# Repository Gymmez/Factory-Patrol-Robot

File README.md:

# 🤖 Za3tar Robot Project

This project shows a robot camera stream and sensor pages in a web browser.

You do not need to install Python. Docker will run everything for you.

## 📦 What You Need

Install these programs:

1. [Docker Desktop](https://www.docker.com/products/docker-desktop/)
2. [Git](https://git-scm.com/downloads)
3. A working camera or phone camera stream

After installing Docker Desktop, open it and wait until it says Docker is
running.

## 1️⃣ Download the Project

Open a terminal:

- **Windows:** open PowerShell
- **Mac:** open Terminal
- **Linux:** open Terminal

Run:

```bash
git clone --recurse-submodules <repository-url>
cd Factory-Patrol-Robot
```

Ask the person who gave you the project for the repository URL.

The `--recurse-submodules` option downloads the `analog_gauge_reader` model
project. If you already cloned the project without submodules, run this from
inside the project folder:

```bash
git submodule update --init --recursive
```

## 2️⃣ Enter the Camera Stream Address

This project needs the address of the camera's MJPEG stream.

The address commonly looks like:

```text
http://192.168.1.50:8080/video
```

Do not use `localhost` or `127.0.0.1`. These addresses refer to the
Docker container, not your camera.

### 📝 Create the settings file

Copy `.env.example` to `.env`:

**Windows PowerShell:**

```powershell
Copy-Item .env.example .env
```

**Mac and Linux:**

```bash
cp .env.example .env
```

Open `.env` in a text editor and replace the address:

```dotenv
MJPEG_STREAM_URL=http://192.168.1.50:8080/video
```

Save the file.

## 3️⃣ Start the Project

In the project folder, run:

```bash
docker compose up -d --build
```

The first start may take a while. Docker must download the database and build
the application. It can take 10 minutes or longer depending on your internet
connection.

Do not close Docker Desktop while building or starting the project.

## 4️⃣ Open the Website

Open a browser and visit:

```text
http://localhost:8000
```

Useful pages:

- Home: http://localhost:8000
- Sensors: http://localhost:8000/sensors
- Camera stream: http://localhost:8000/stream
- Robot controls: http://localhost:8000/control
- Health check: http://localhost:8000/health
- API documentation: http://localhost:8000/docs

## 5️⃣ Change the Camera Address

To use another camera address:

1. Open `.env`.
2. Change `MJPEG_STREAM_URL`.
3. Save the file.
4. Run:

```bash
docker compose up -d --force-recreate api
```

Refresh the website.

## ✅ Check Whether It Is Working

Run:

```bash
docker compose ps
```

You should see the `api` and `db` containers running.

For the health check:

```bash
curl http://localhost:8000/health
```

A successful response is:

```json
{"status":"ok"}
```

If the camera is not visible, confirm that:

- The camera address is correct.
- The address works from a normal browser or phone.
- The address is reachable from the computer running Docker.
- The address ends with the correct video path.

## 🛑 Stop the Project

Keep the saved data and stop the containers:

```bash
docker compose down
```

Start it again later:

```bash
docker compose up -d
```

## 🔄 Reset Everything

This permanently deletes all saved database data.

```bash
docker compose down -v
docker compose up -d --build
```

Only use this command when a complete reset is wanted.

## 🧰 If Something Goes Wrong

### ⚠️ The project does not start

Check that Docker Desktop is running, then run:

```bash
docker compose up --build
```

Reading the messages in the terminal can show whether Docker is downloading
or building something.

### 📹 The camera does not appear

Open the camera address directly in a browser.

Example:

```text
http://192.168.1.50:8080/video
```

If that address does not open in the browser, the application cannot receive
the stream.

### 🔍 Show recent errors

```bash
docker compose logs api
docker compose logs db
```

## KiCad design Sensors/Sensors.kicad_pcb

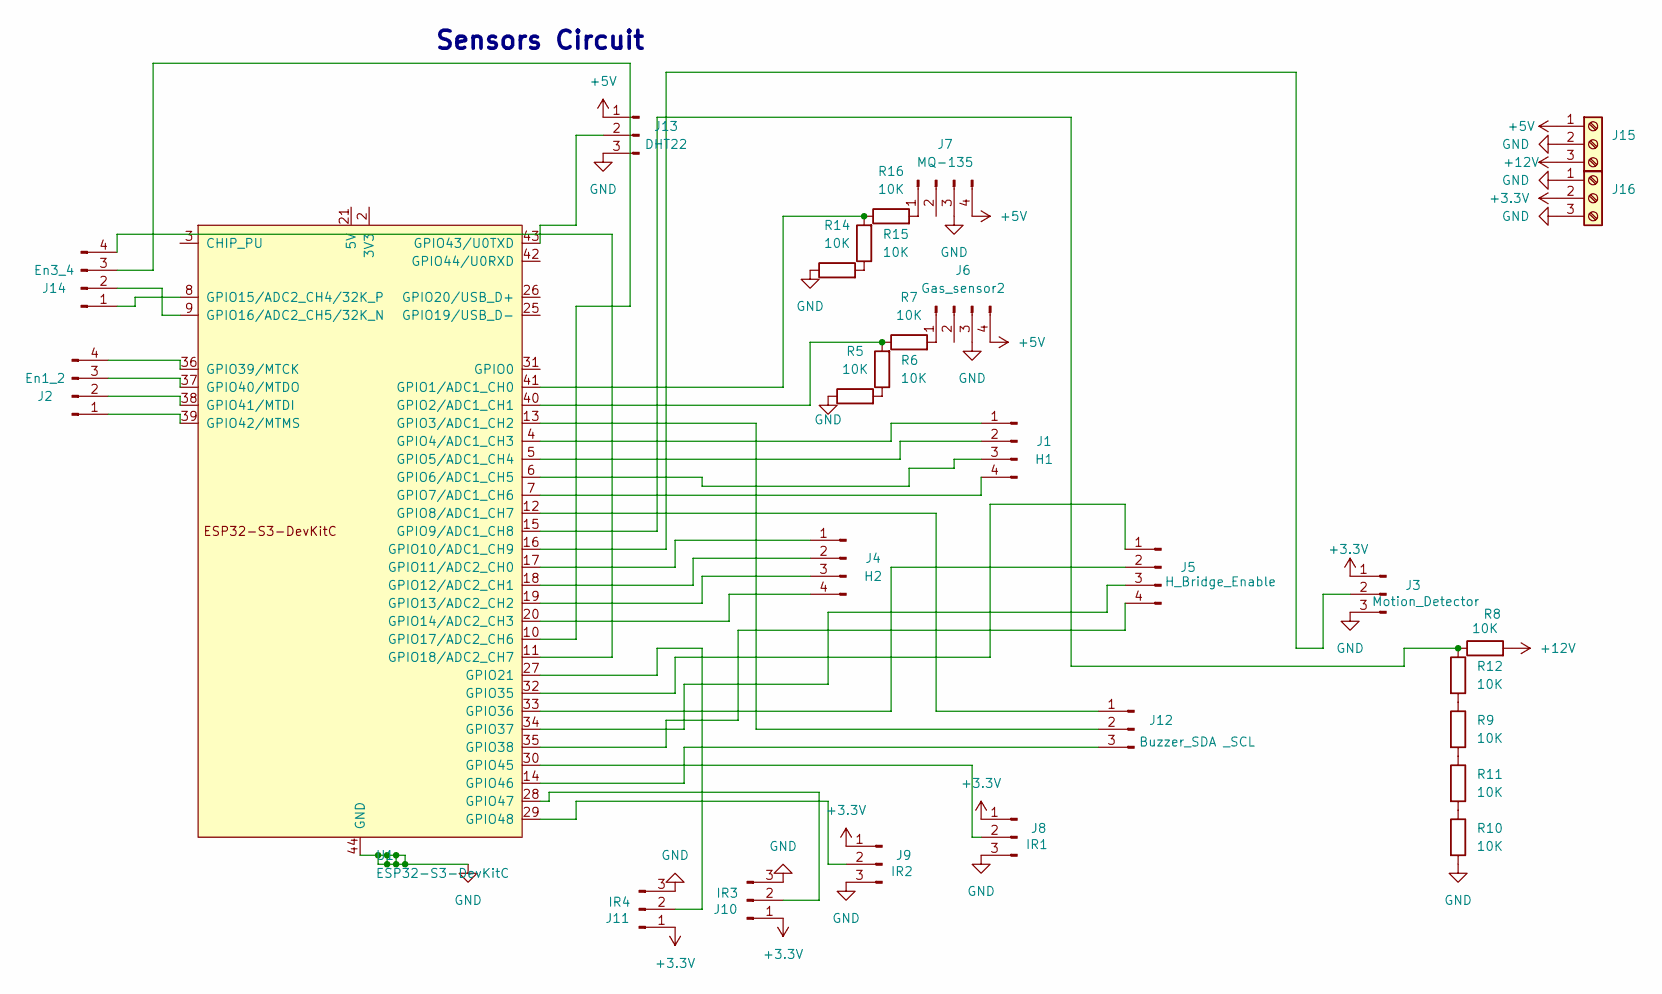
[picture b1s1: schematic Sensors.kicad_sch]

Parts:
J1: H1; PinSocket_1x04_P2.54mm_Vertical
J2: En1_2; PinSocket_1x04_P2.54mm_Vertical
J3: Motion_Detector; PinSocket_1x03_P2.54mm_Vertical
J4: H2; PinSocket_1x04_P2.54mm_Vertical
J5: H_Bridge_Enable; PinSocket_1x04_P2.54mm_Vertical
J6: Gas_sensor2; PinSocket_1x04_P2.54mm_Vertical
J7: MQ-135; PinSocket_1x04_P2.54mm_Vertical
J8: IR1; PinSocket_1x03_P2.54mm_Vertical
J9: IR2; PinSocket_1x03_P2.54mm_Vertical
J10: IR3; PinSocket_1x03_P2.54mm_Vertical
J11: IR4; PinSocket_1x03_P2.54mm_Vertical
J12: Buzzer_SDA _SCL; PinSocket_1x03_P2.54mm_Vertical
J13: DHT22; PinSocket_1x03_P2.54mm_Vertical
J14: En3_4; PinSocket_1x04_P2.54mm_Vertical
J15, J16: Screw_Terminal_01x03; TerminalBlock_Phoenix_MKDS-3-3-5.08_1x03_P5.08mm_Horizontal
R5, R6, R7, R8, R9, R10, R11, R12, R14, R15, R16: 10K; R_Axial_DIN0207_L6.3mm_D2.5mm_P7.62mm_Horizontal
U1: ESP32-S3-DevKitC

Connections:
+3.3V: J3.1, J8.1, J9.1, J10.1, J11.1, J16.2
+5V: J6.4, J7.4, J13.1, J15.1
+12V: J15.3, R8.2
GND: J3.3, J6.3, J7.3, J8.3, J9.3, J10.3, J11.3, J13.3, J15.2, J16.1, J16.3, R5.1, R10.2, R14.1, U1.22 (GND), U1.23 (GND), U1.24 (GND), U1.44 (GND)
unnamed: J1.1, U1.4 (GPIO4/ADC1_CH3)
unnamed: J1.2, U1.5 (GPIO5/ADC1_CH4)
unnamed: J1.3, U1.6 (GPIO6/ADC1_CH5)
unnamed: J1.4, U1.7 (GPIO7/ADC1_CH6)
unnamed: J2.1, U1.39 (GPIO42/MTMS)
unnamed: J2.2, U1.38 (GPIO41/MTDI)
unnamed: J2.3, U1.37 (GPIO40/MTDO)
unnamed: J2.4, U1.36 (GPIO39/MTCK)
unnamed: J3.2, U1.16 (GPIO10/ADC1_CH9)
unnamed: J4.1, U1.17 (GPIO11/ADC2_CH0)
unnamed: J4.2, U1.18 (GPIO12/ADC2_CH1)
unnamed: J4.3, U1.19 (GPIO13/ADC2_CH2)
unnamed: J4.4, U1.20 (GPIO14/ADC2_CH3)
unnamed: J5.1, U1.32 (GPIO35)
unnamed: J5.2, U1.33 (GPIO36)
unnamed: J5.3, U1.34 (GPIO37)
unnamed: J5.4, U1.35 (GPIO38)
unnamed: J6.1, R7.2
unnamed: J7.1, R16.2
unnamed: J8.2, U1.30 (GPIO45)
unnamed: J9.2, U1.29 (GPIO48)
unnamed: J10.2, U1.28 (GPIO47)
unnamed: J11.2, U1.27 (GPIO21)
unnamed: J12.1, U1.12 (GPIO8/ADC1_CH7)
unnamed: J12.2, U1.13 (GPIO3/ADC1_CH2)
unnamed: J12.3, U1.14 (GPIO46)
unnamed: J13.2, U1.43 (GPIO43/U0TXD)
unnamed: J14.1, U1.8 (GPIO15/ADC2_CH4/32K_P)
unnamed: J14.2, U1.9 (GPIO16/ADC2_CH5/32K_N)
unnamed: J14.3, U1.10 (GPIO17/ADC2_CH6)
unnamed: J14.4, U1.11 (GPIO18/ADC2_CH7)
unnamed: R5.2, R6.1
unnamed: R10.1, R11.2
unnamed: R9.2, R11.1
unnamed: R9.1, R12.2
unnamed: R14.2, R15.1
unnamed: U1.1 (3V3), U1.2 (3V3)
unnamed: R15.2, R16.1, U1.41 (GPIO1/ADC1_CH0)
unnamed: R6.2, R7.1, U1.40 (GPIO2/ADC1_CH1)
unnamed: R8.1, R12.1, U1.15 (GPIO9/ADC1_CH8)

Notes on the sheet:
Sensors Circuit

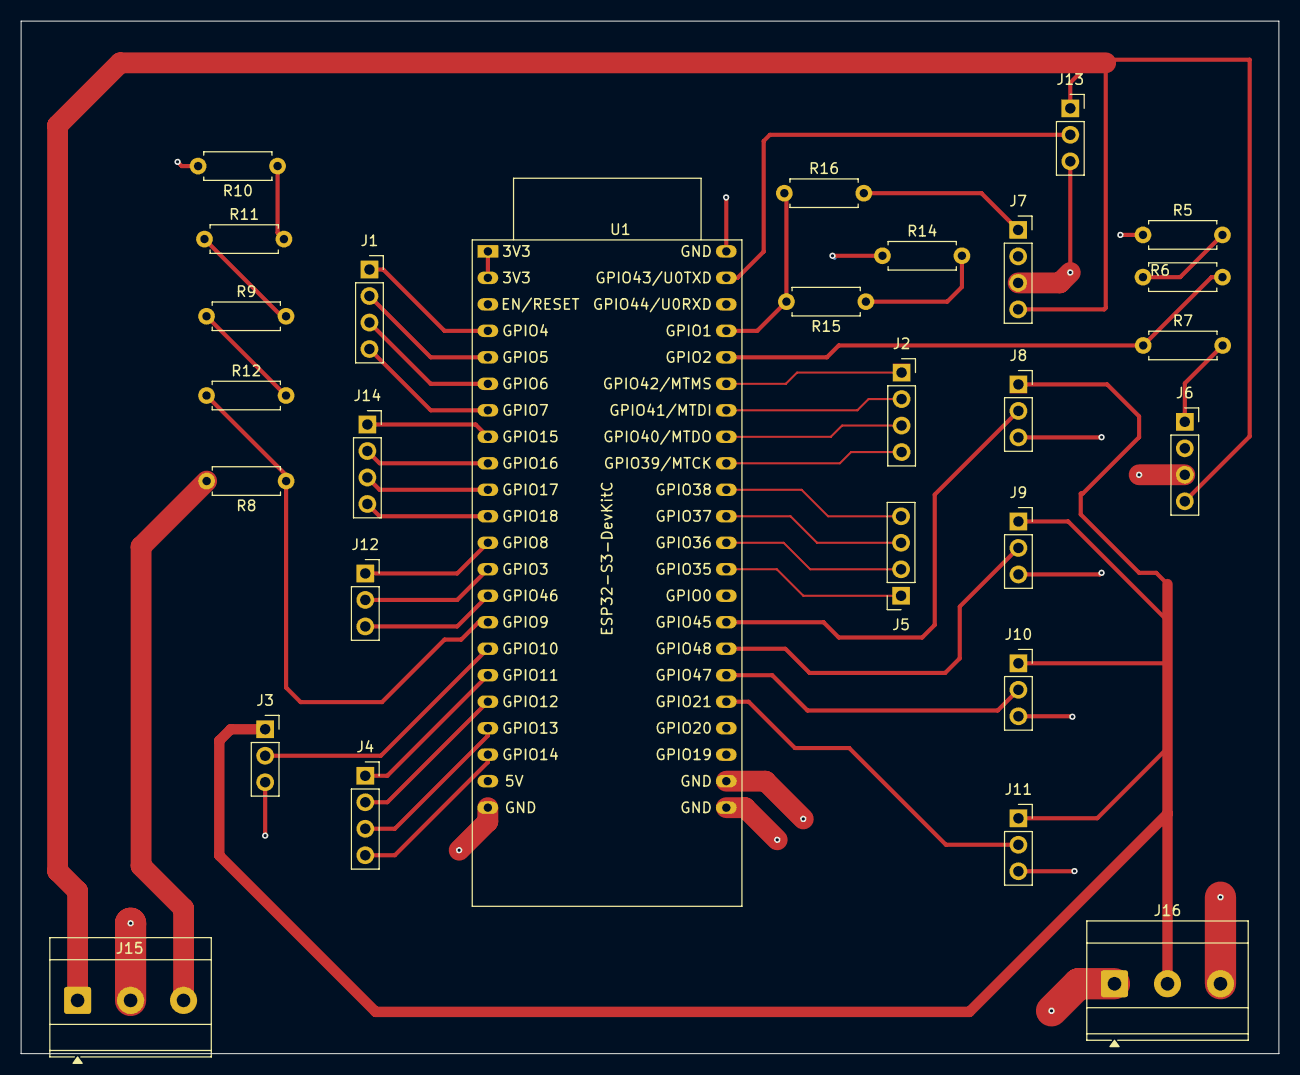
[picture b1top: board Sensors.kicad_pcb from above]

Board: 2 copper layers, 120.6 x 99.0 mm, 28 parts (0 on the bottom side), 44 nets.
